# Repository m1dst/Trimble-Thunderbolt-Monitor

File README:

This is a hardware and software project to monitor and command a Trimble Thunderbolt which is a GPS disciplined 10MHz reference.

The software runs on a Netduino which is a .net version of the popular Arduino platform.  It also includes a shield to make connecting it up to the Netduino much cleaner.  I have designed the shield to be compatible with both Netduino are Arduino in case someone wants to port to the other platform.

Blog posts can be found at http://www.m1dst.co.uk/category/projects/trimble-thunderbolt-monitor/

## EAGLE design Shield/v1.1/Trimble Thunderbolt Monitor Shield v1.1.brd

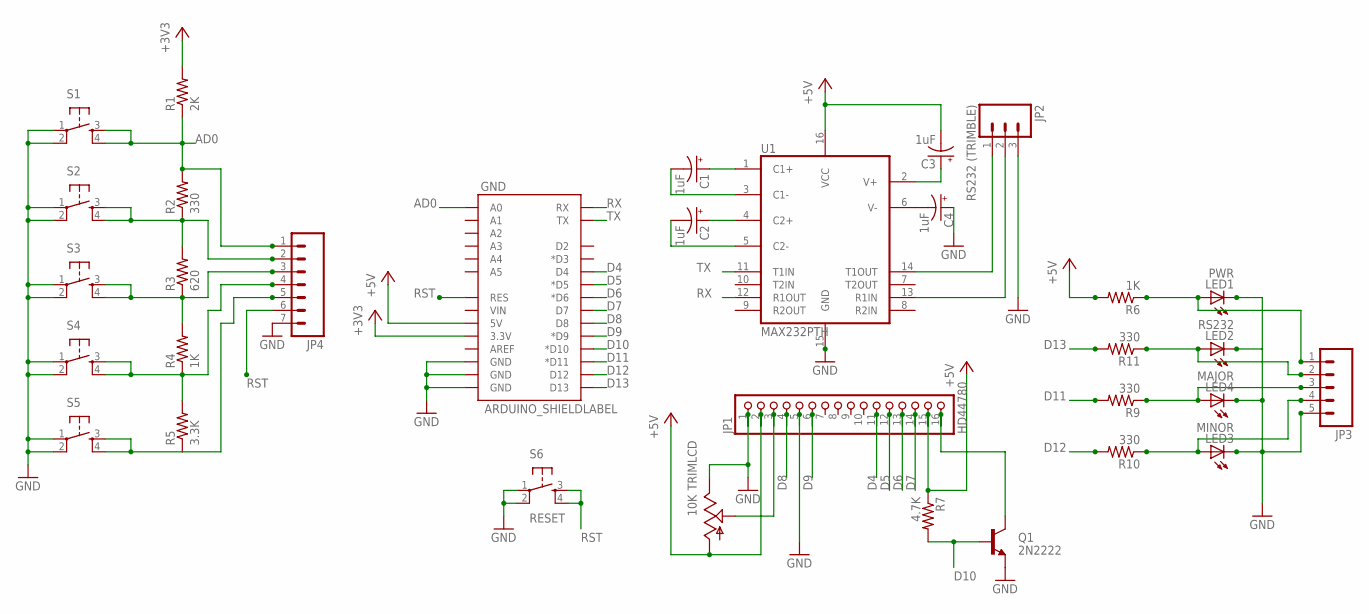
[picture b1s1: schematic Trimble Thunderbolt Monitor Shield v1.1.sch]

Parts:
C1, C2, C3, C4: 1uF; CPOL-RADIAL-10UF-25V
GND: ARDUINO_SHIELDLABEL; DUEMILANOVE_SHIELD
JP1: HD44780; 1X16
JP2: RS232 (TRIMBLE); MOLEX-1X3
JP3: M05PTH; 1X05
JP4: M07; 1X07
LED1: PWR; LED5MM
LED2: RS232; LED5MM
LED3: MINOR; LED5MM
LED4: MAJOR; LED5MM
Q1: 2N2222; TO-92-AMMO
R1: 2K; AXIAL-0.3
R2, R9, R10, R11: 330; AXIAL-0.3
R3: 620; AXIAL-0.3
R4, R6: 1K; AXIAL-0.3
R5: 3.3K; AXIAL-0.3
R7: 4.7K; AXIAL-0.3
S1, S2, S3, S4, S5: TAC_SWITCHPTH; TACTILE-PTH
S6: RESET; TACTILE-PTH
TRIMLCD: 10K; 3362U
U1: MAX232PTH; DIL16

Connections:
+3V3: GND.3.3V, R1.P$2 (2)
+5V: C3.2 (-), GND.5V, JP1.2, JP1.15, R6.P$2 (2), R7.P$1 (1), TRIMLCD.P$3 (A), U1.16 (VCC)
AD0: GND.A0, JP4.1, R1.P$1 (1), R2.P$2 (2), S1.3, S1.4
D4: GND.D4, JP1.11
D5: GND.D5 (*D5), JP1.12
D6: GND.D6 (*D6), JP1.13
D7: GND.D7, JP1.14
D8: GND.D8, JP1.4
D9: GND.D9 (*D9), JP1.6
D10: GND.D10 (*D10), Q1.2 (B), R7.P$2 (2)
D11: GND.D11 (*D11), R9.P$2 (2)
D12: GND.D12, R10.P$2 (2)
D13: GND.D13, R11.P$2 (2)
GND: C4.1 (+), GND.GND@0 (GND), GND.GND@1 (GND), GND.GND@2 (GND), JP1.1, JP1.5, JP2.3, JP3.5, JP4.7, LED1.K (C), LED2.K (C), LED3.K (C), LED4.K (C), Q1.1 (E), S1.1, S1.2, S2.1, S2.2, S3.1, S3.2, S4.1, S4.2, S5.1, S5.2, S6.1, S6.2, TRIMLCD.P$1 (E), U1.15 (GND)
LEDRS232: JP3.2, LED2.A, R11.P$1 (1)
unnamed: JP4.3, R3.P$1 (1), R4.P$2 (2), S3.3, S3.4
unnamed: JP3.3, LED4.A, R9.P$1 (1)
unnamed: JP4.4, R4.P$1 (1), R5.P$2 (2), S4.3, S4.4
unnamed: JP3.1, LED1.A, R6.P$1 (1)
unnamed: JP4.5, R5.P$1 (1), S5.3, S5.4
unnamed: JP2.1, U1.14 (T1OUT)
unnamed: JP1.16, Q1.3 (C)
unnamed: JP1.3, TRIMLCD.P$2 (S)
unnamed: JP2.2, U1.13 (R1IN)
unnamed: C1.2 (-), U1.3 (C1-)
unnamed: C1.1 (+), U1.1 (C1+)
unnamed: C2.1 (+), U1.4 (C2+)
unnamed: C2.2 (-), U1.5 (C2-)
unnamed: C4.2 (-), U1.6 (V-)
unnamed: C3.1 (+), U1.2 (V+)
unnamed: JP3.4, LED3.A, R10.P$1 (1)
unnamed: JP4.2, R2.P$1 (1), R3.P$2 (2), S2.3, S2.4
RST: GND.RES, JP4.6, S6.3, S6.4
RX: GND.RX, U1.12 (R1OUT)
TX: GND.TX, U1.11 (T1IN)

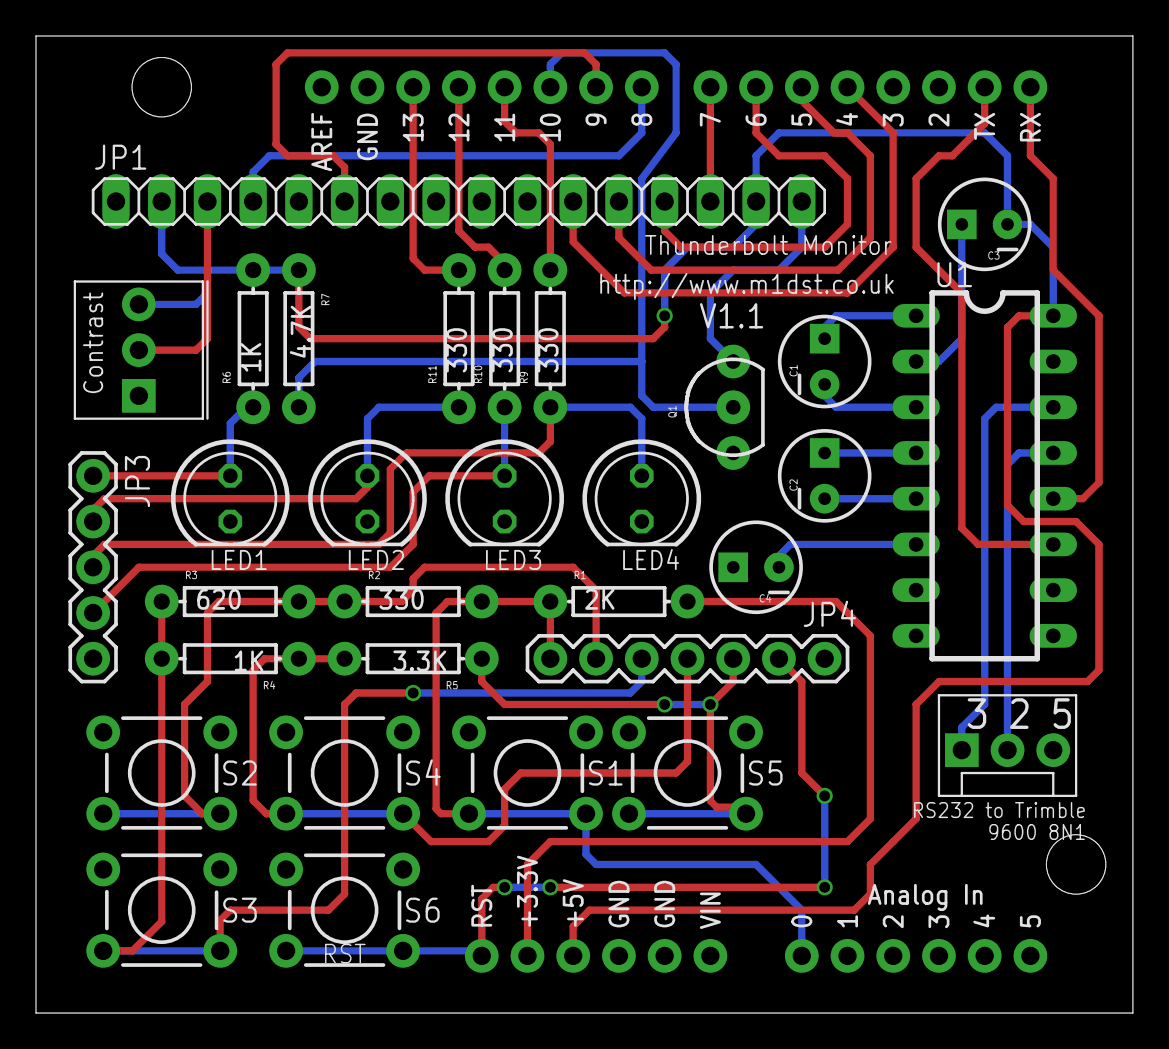
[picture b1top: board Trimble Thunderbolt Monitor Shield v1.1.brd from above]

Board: 2 copper layers, 60.9 x 54.3 mm, 32 parts (0 on the bottom side), 35 nets.

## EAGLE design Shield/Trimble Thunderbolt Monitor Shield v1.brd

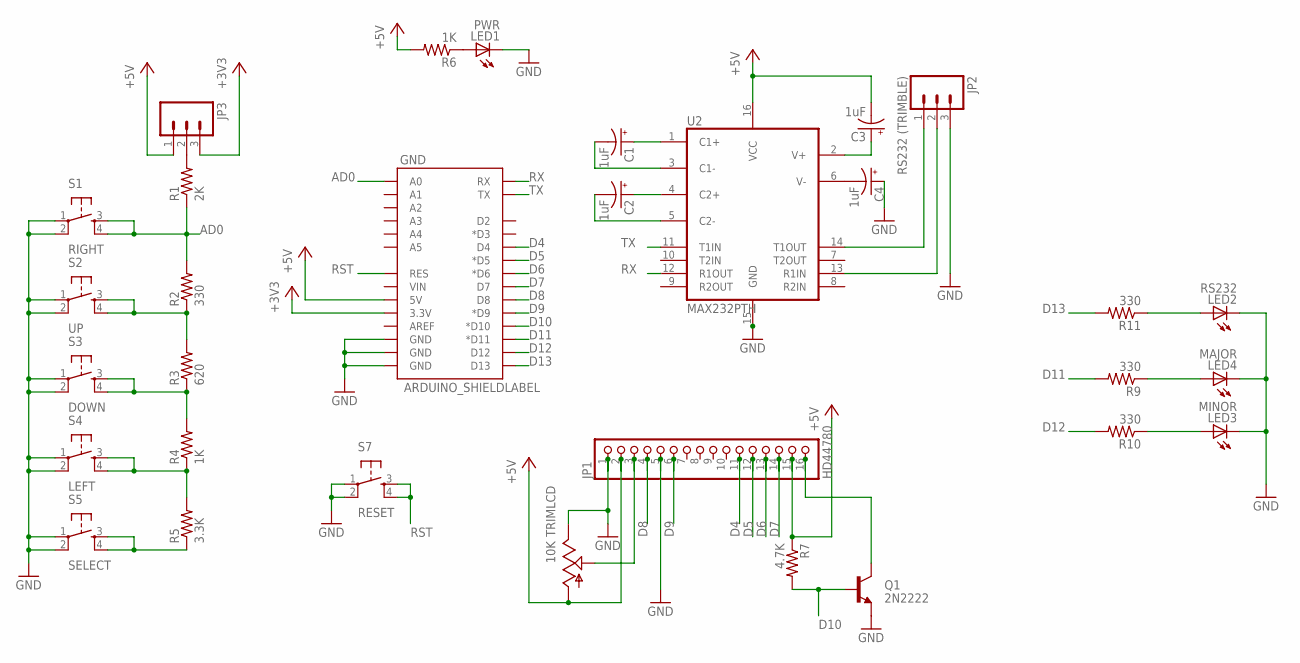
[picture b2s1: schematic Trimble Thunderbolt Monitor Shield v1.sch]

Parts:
C1, C2, C3, C4: 1uF; CPOL-RADIAL-10UF-25V
GND: ARDUINO_SHIELDLABEL; DUEMILANOVE_SHIELD
JP1: HD44780; 1X16
JP2: RS232 (TRIMBLE); MOLEX-1X3
JP3: M03PTH; 1X03
LED1: PWR; LED5MM
LED2: RS232; LED5MM
LED3: MINOR; LED5MM
LED4: MAJOR; LED5MM
Q1: 2N2222; TO-92-AMMO
R1: 2K; AXIAL-0.3
R2, R9, R10, R11: 330; AXIAL-0.3
R3: 620; AXIAL-0.3
R4, R6: 1K; AXIAL-0.3
R5: 3.3K; AXIAL-0.3
R7: 4.7K; AXIAL-0.3
S1: RIGHT; TACTILE-PTH
S2: UP; TACTILE-PTH
S3: DOWN; TACTILE-PTH
S4: LEFT; TACTILE-PTH
S5: SELECT; TACTILE-PTH
S7: RESET; TACTILE-PTH
TRIMLCD: 10K; 3362U
U2: MAX232PTH; DIL16

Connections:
+3V3: GND.3.3V, JP3.3
+5V: C3.2 (-), GND.5V, JP1.2, JP1.15, JP3.1, R6.P$2 (2), R7.P$1 (1), TRIMLCD.P$3 (A), U2.16 (VCC)
AD0: GND.A0, R1.P$1 (1), R2.P$2 (2), S1.3, S1.4
D4: GND.D4, JP1.11
D5: GND.D5 (*D5), JP1.12
D6: GND.D6 (*D6), JP1.13
D7: GND.D7, JP1.14
D8: GND.D8, JP1.4
D9: GND.D9 (*D9), JP1.6
D10: GND.D10 (*D10), Q1.2 (B), R7.P$2 (2)
D11: GND.D11 (*D11), R9.P$2 (2)
D12: GND.D12, R10.P$2 (2)
D13: GND.D13, R11.P$2 (2)
GND: C4.1 (+), GND.GND@0 (GND), GND.GND@1 (GND), GND.GND@2 (GND), JP1.1, JP1.5, JP2.3, LED1.K (C), LED2.K (C), LED3.K (C), LED4.K (C), Q1.1 (E), S1.1, S1.2, S2.1, S2.2, S3.1, S3.2, S4.1, S4.2, S5.1, S5.2, S7.1, S7.2, TRIMLCD.P$1 (E), U2.15 (GND)
LEDRS232: LED2.A, R11.P$1 (1)
unnamed: R3.P$1 (1), R4.P$2 (2), S3.3, S3.4
unnamed: LED4.A, R9.P$1 (1)
unnamed: R4.P$1 (1), R5.P$2 (2), S4.3, S4.4
unnamed: LED1.A, R6.P$1 (1)
unnamed: R5.P$1 (1), S5.3, S5.4
unnamed: JP2.1, U2.14 (T1OUT)
unnamed: JP1.16, Q1.3 (C)
unnamed: JP1.3, TRIMLCD.P$2 (S)
unnamed: JP2.2, U2.13 (R1IN)
unnamed: C1.2 (-), U2.3 (C1-)
unnamed: C1.1 (+), U2.1 (C1+)
unnamed: C2.1 (+), U2.4 (C2+)
unnamed: C2.2 (-), U2.5 (C2-)
unnamed: C4.2 (-), U2.6 (V-)
unnamed: C3.1 (+), U2.2 (V+)
unnamed: LED3.A, R10.P$1 (1)
unnamed: JP3.2, R1.P$2 (2)
unnamed: R2.P$1 (1), R3.P$2 (2), S2.3, S2.4
RST: GND.RES, S7.3, S7.4
RX: GND.RX, U2.12 (R1OUT)
TX: GND.TX, U2.11 (T1IN)

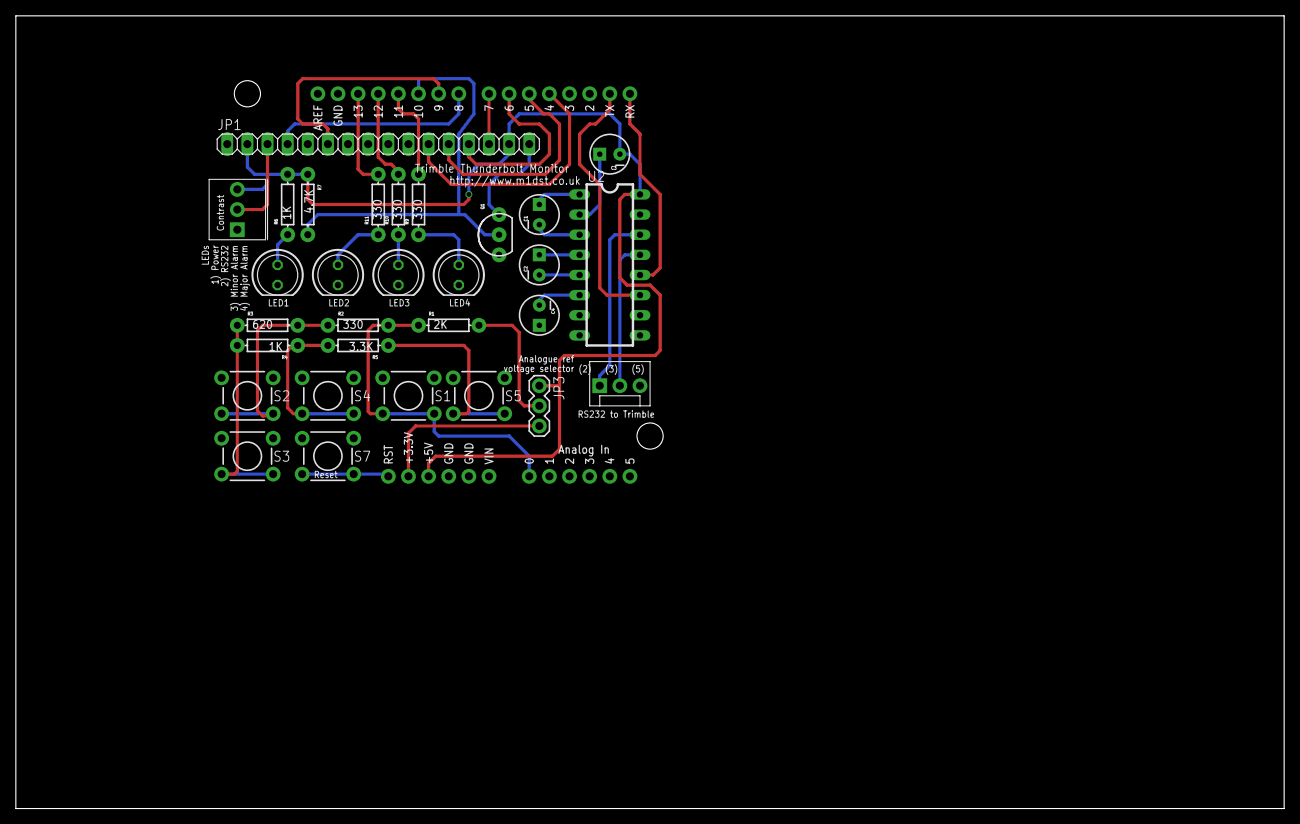
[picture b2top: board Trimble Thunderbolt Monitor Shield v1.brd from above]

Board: 2 copper layers, 160.0 x 100.0 mm, 31 parts (0 on the bottom side), 36 nets.

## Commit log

2013-03-15 Initial check in
    This is the first version of the Trimble Thunderbolt Shield. I have
    done my best to check it but as yet it hasn't been fabricated so please
    check it yourself if you are going to create one.
2013-03-15 Added README
2013-03-15 Updated README (again)
2013-03-15 README (again)
2013-03-18 Changed the pot used for LCD contrast to a 3362U package.
2013-03-18 Backlight and track routing changes
    Changes to the layout of some of the tracks to make them look neater.
    Also changed the way the backlight interacts with the Netduino. It is
    now possible to control the brightness of the LCD via a pin on the
    Netduino.
    Also changed some of the LED output pins
2013-03-18 A few silkscreen changes
2013-03-18 Updated some more silkscreen items, a few traces and added gerber files.
2013-03-20 Fixed typo in readme
2013-03-20 Further annotation to readme as I experiment with markdown
2013-06-04 Initial check in of the software
    This is my initial version of the software required to run on the
    Netduino Plus 2. I am aware that there are one or two bugs which cause
    the Netduino to lock up. If you can reproduce them then please let me
    know so I can fix (or submit a pull request)
2013-06-15 Fixed crash due to longer Lat/Long than expected.
    I was advised by Steve Jacobs that his monitor crashed. We identified
    the problem to be a difference in length between his Lat/Long and mine.
    I have modified the code to pad accordingly whitespace when needed.
    Tested and still works fine on my monitor. Also bumped the version to
    1.0.3.
2013-06-15 Fixed crash due to longer Lat/Long than expected.
    Could still have failed if the longitude became 3 digits and negative.
2013-06-15 Updated the project description
2013-07-05 Added instructions document
2013-07-05 Allow unsafe code to be compiled.
    Not sure why this got disabled.
2013-07-05 Updated the readme
    Now contains link to purchase the kit.
2013-11-25 Enhanced the manual
    Added information to the manual to explain the use of the buttons.
2014-01-19 Created v1.1
    Added a new version of the shield. I’ve added headers for external
    buttons and LEDs rather than soldering directly to the board. The
    manual has been updated with these changes.
    Various components have been renamed to make the numbering more
    consistent.
2014-02-04 Fixed some silkscreen issues
2014-02-04 Removed old berbers
2014-02-04 Fixed some ERC issues
2014-02-04 Updated the manuals
    Updated the schematic, and button instructions to make it clearer which
    button is which. There is still work required to label the new headers
    on v1.1
2014-02-05 Example LCD Image
    A photo of a typical LCD once the monitor is running.
2014-04-22 Subtle cleanup of the v1.1 board and gerber files
2014-04-22 Changed board font to vector
2017-07-17 Added a project to cover the Netduino 1
2017-07-31 Fixed the issue with the GPS week rollover.
    The Trimble Thunderbolt is no longer reliable after July 30th 2017. The
    date needs to be manually calculated from now on. We add 1024 to the
    GPS week number and then manually work out the new time including the
    leap second offset.
2017-07-31 Warn existing users there is an code update which should be used.
2017-08-02 Update the readme
2017-08-10 Added support for FEZ Lemur
    Changed the namespaces to make them simpler.
    Add .vs to the gitignore file.
    Add shared AssemblyInfo file.
    Create project files for each type of board with shared files.
    Updated the instructions to reflect new projects.
2017-10-29 Updated the docs
2017-10-31 Fixed a broken link in the instructions
2017-11-04 Updated the documentation
2017-11-07 No longer show the survey as 0% complete when no survey is in progress.
    Bumped to v1.0.5
2017-11-07 Added an "uptime" indicator where the survey text used to be.
2017-11-13 Refactoring
2017-11-24 Add some guidance on how to download the software.
2017-11-28 Added a link for the direct download to VS2013.
2018-02-18 Add support for LCD backlight brightness #1
    This is experimental. If you find any issues with hanging we should
    roll this feature back.
2018-02-18 Bumped the version number to 1.0.7
2019-07-10 Satellite signal strength and additional information
    Fix the incorrect constraints list
    General refactoring
    Bumped to v1.1.0
2019-07-10 Ported to TinyCLR so it can be run on a 10$ Fez
    Bumped to version 2.0.0
2019-07-10 Fixes to v1.1.0
2019-07-10 v1.1.0 Optimisations
2019-07-10 v2.0.0 Optimisations
2019-07-10 Fix - "screen number not showing on #4"
2019-07-11 Better display of debug packets. Correctly converts a byte to hex as String.Format isn't supported.
2019-08-08 Added timeout for tracked sats if no update received within 2 and 10s
    Bumped to v1.1.1 and 2.0.1
    Add more debugging statements
2019-08-30 Remove a debug statement.
2019-09-04 Added a watchdog to the TinyCLR version to allow recovery.
    The watchdog timeout is currently 30s and is being reset at the start of every loop.

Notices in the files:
parts and their libraries:
SparkFun: Licensing: CC v3.0 Share-Alike You are welcome to use this library for commercial purposes.
